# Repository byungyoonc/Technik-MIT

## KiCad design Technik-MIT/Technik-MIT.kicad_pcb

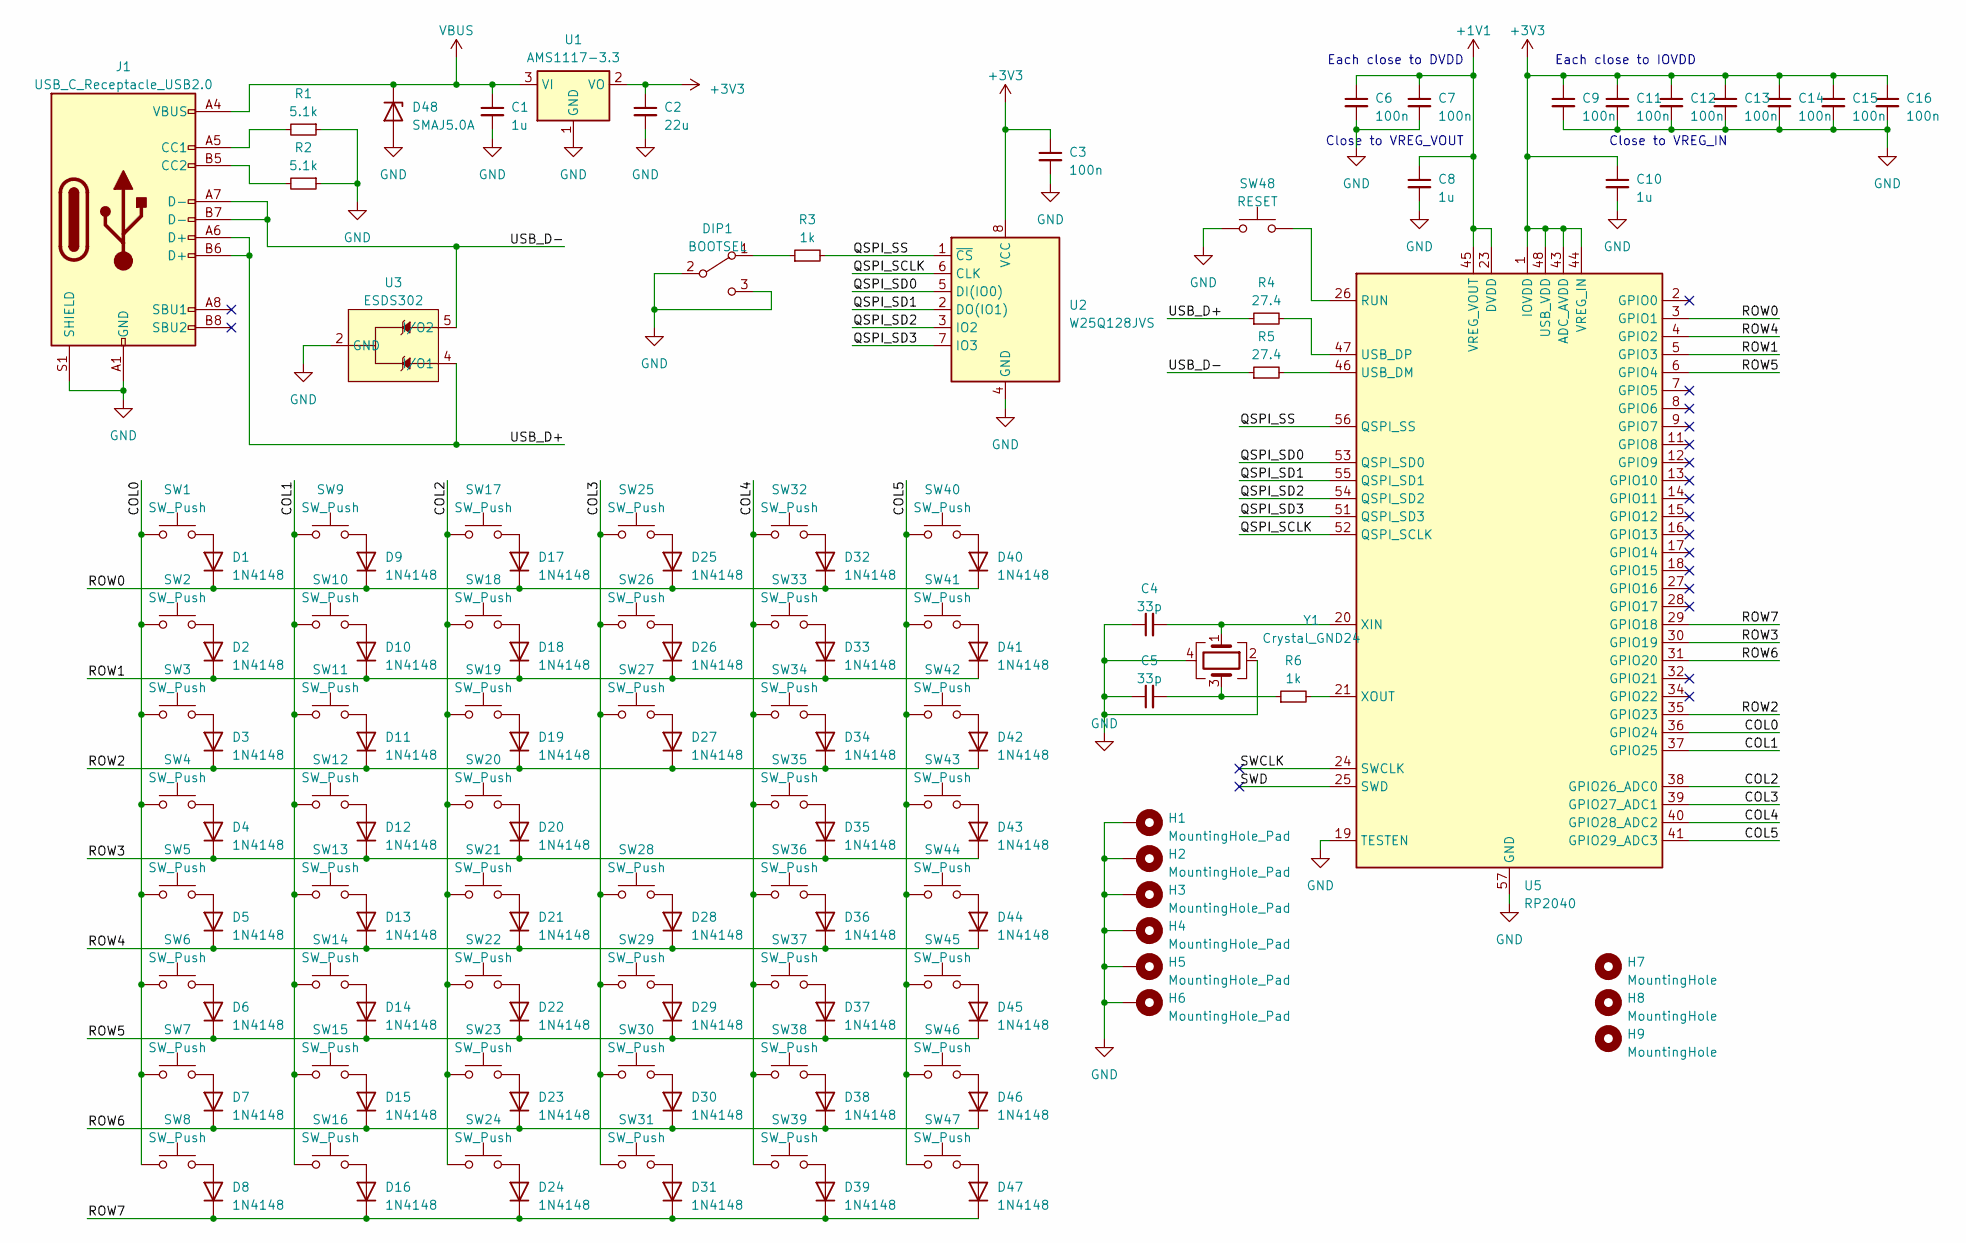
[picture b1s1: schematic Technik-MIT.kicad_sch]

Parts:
C1, C8, C10: 1u; C_0402_1005Metric
C2: 22u; C_0603_1608Metric
C3, C6, C7, C9, C11, C12, C13, C14, C15, C16: 100n; C_0402_1005Metric
C4, C5: 33p; C_0402_1005Metric
D1, D2, D3, D4, D5, D6, D7, D8, D9, D10, D11, D12, D13, D14, D15, D16, D17, D18, D19, D20, D21, D22, D23, D24, D25, D26, D27, D28, D29, D30, D31, D32, D33, D34, D35, D36, D37, D38, D39, D40, D41, D42, D43, D44, D45, D46, D47: 1N4148; D_SOD-123
D48: SMAJ5.0A; D_SMA; LCSC C2925443
DIP1: BOOTSEL; SW_SPDT_PCM12; LCSC C431541
H1, H2, H3, H4, H5, H6: MountingHole_Pad; Standoff_Hole
H7, H8, H9: MountingHole; Tooling Hole
J1: USB_C_Receptacle_USB2.0; Molex-216990_GCT-USB45xx_HRO-TYPE-C-31-M-13x; LCSC C3019717
R1, R2: 5.1k; R_0402_1005Metric
R3, R6: 1k; R_0402_1005Metric
R4, R5: 27.4; R_0603_1608Metric
SW1, SW2, SW3, SW4, SW5, SW6, SW7, SW8, SW9, SW10, SW11, SW12, SW13, SW14, SW15, SW16, SW17, SW18, SW19, SW20, SW21, SW22, SW23, SW24, SW25, SW26, SW27, SW28, SW29, SW30, SW31, SW32, SW33, SW34, SW35, SW36, SW37, SW38, SW39, SW41, SW42, SW43, SW45, SW46, SW47: SW_Push; ChocV1_Hotswap
SW40: SW_Push; ChocV1_Hotswap_WO_UpperRight
SW44: SW_Push; ChocV1_Hotswap_WO_UpperLeft
SW48: RESET; SW_SPST_TL3342; LCSC C318884
U1: AMS1117-3.3; SOT-223-3_TabPin2
U2: W25Q128JVS; SOIC-8_5.23x5.23mm_P1.27mm; LCSC C97521
U3: ESDS302; SOT-23-5
U5: RP2040; QFN-56-1EP_7x7mm_P0.4mm_EP3.2x3.2mm
Y1: Crystal_GND24; Crystal_SMD_3225-4Pin_3.2x2.5mm; LCSC C9002

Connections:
+1V1: C6.1, C7.1, C8.1, U5.23 (DVDD), U5.45 (VREG_VOUT), U5.50 (DVDD)
+3V3: C2.1, C3.1, C9.1, C10.1, C11.1, C12.1, C13.1, C14.1, C15.1, C16.1, U1.2 (VO), U2.8 (VCC), U5.1 (IOVDD), U5.10 (IOVDD), U5.22 (IOVDD), U5.33 (IOVDD), U5.42 (IOVDD), U5.43 (ADC_AVDD), U5.44 (VREG_IN), U5.48 (USB_VDD), U5.49 (IOVDD)
/COL0: SW1.1, SW2.1, SW3.1, SW4.1, SW5.1, SW6.1, SW7.1, SW8.1, U5.36 (GPIO24)
/COL1: SW9.1, SW10.1, SW11.1, SW12.1, SW13.1, SW14.1, SW15.1, SW16.1, U5.37 (GPIO25)
/COL2: SW17.1, SW18.1, SW19.1, SW20.1, SW21.1, SW22.1, SW23.1, SW24.1, U5.38 (GPIO26_ADC0)
/COL3: SW25.1, SW26.1, SW27.1, SW28.1, SW29.1, SW30.1, SW31.1, U5.39 (GPIO27_ADC1)
/COL4: SW32.1, SW33.1, SW34.1, SW35.1, SW36.1, SW37.1, SW38.1, SW39.1, U5.40 (GPIO28_ADC2)
/COL5: SW40.1, SW41.1, SW42.1, SW43.1, SW44.1, SW45.1, SW46.1, SW47.1, U5.41 (GPIO29_ADC3)
/QSPI_SCLK: U2.6 (CLK), U5.52 (QSPI_SCLK)
/QSPI_SD0: U2.5 (DI(IO0)), U5.53 (QSPI_SD0)
/QSPI_SD1: U2.2 (DO(IO1)), U5.55 (QSPI_SD1)
/QSPI_SD2: U2.3 (IO2), U5.54 (QSPI_SD2)
/QSPI_SD3: U2.7 (IO3), U5.51 (QSPI_SD3)
/QSPI_SS: R3.2, U2.1 (~CS), U5.56 (QSPI_SS)
/ROW0: D1.1 (K), D9.1 (K), D17.1 (K), D25.1 (K), D32.1 (K), D40.1 (K), U5.3 (GPIO1)
/ROW1: D2.1 (K), D10.1 (K), D18.1 (K), D26.1 (K), D33.1 (K), D41.1 (K), U5.5 (GPIO3)
/ROW2: D3.1 (K), D11.1 (K), D19.1 (K), D27.1 (K), D34.1 (K), D42.1 (K), U5.35 (GPIO23)
/ROW3: D4.1 (K), D12.1 (K), D20.1 (K), D35.1 (K), D43.1 (K), U5.30 (GPIO19)
/ROW4: D5.1 (K), D13.1 (K), D21.1 (K), D28.1 (K), D36.1 (K), D44.1 (K), U5.4 (GPIO2)
/ROW5: D6.1 (K), D14.1 (K), D22.1 (K), D29.1 (K), D37.1 (K), D45.1 (K), U5.6 (GPIO4)
/ROW6: D7.1 (K), D15.1 (K), D23.1 (K), D30.1 (K), D38.1 (K), D46.1 (K), U5.31 (GPIO20)
/ROW7: D8.1 (K), D16.1 (K), D24.1 (K), D31.1 (K), D39.1 (K), D47.1 (K), U5.29 (GPIO18)
/SWCLK: U5.24 (SWCLK)
/SWD: U5.25 (SWD)
/USB_D+: J1.A6 (D+), J1.B6 (D+), R4.1, U3.3 (NC), U3.4 (I/O1)
/USB_D-: J1.A7 (D-), J1.B7 (D-), R5.1, U3.1 (NC), U3.5 (I/O2)
GND: C1.2, C2.2, C3.2, C4.1, C5.1, C6.2, C7.2, C8.2, C9.2, C10.2, C11.2, C12.2, C13.2, C14.2, C15.2, C16.2, D48.2 (A), DIP1.2 (B), DIP1.3 (C), H1.1, H2.1, H3.1, H4.1, H5.1, H6.1, J1.A1 (GND), J1.A12 (GND), J1.B1 (GND), J1.B12 (GND), J1.S1 (SHIELD), R1.1, R2.1, SW48.1, U1.1 (GND), U2.4 (GND), U3.2 (GND), U5.19 (TESTEN), U5.57 (GND), Y1.2, Y1.4; also elsewhere on the board
unnamed: C5.2, R6.1, Y1.3
unnamed: D1.2 (A), SW1.2
unnamed: D2.2 (A), SW2.2
unnamed: D3.2 (A), SW3.2
unnamed: D4.2 (A), SW4.2
unnamed: D5.2 (A), SW5.2
unnamed: D6.2 (A), SW6.2
unnamed: D7.2 (A), SW7.2
unnamed: D8.2 (A), SW8.2
unnamed: D9.2 (A), SW9.2
unnamed: D10.2 (A), SW10.2
unnamed: D11.2 (A), SW11.2
unnamed: D12.2 (A), SW12.2
unnamed: D13.2 (A), SW13.2
unnamed: D14.2 (A), SW14.2
unnamed: D15.2 (A), SW15.2
unnamed: D16.2 (A), SW16.2
unnamed: D17.2 (A), SW17.2
unnamed: D18.2 (A), SW18.2
unnamed: D19.2 (A), SW19.2
unnamed: D20.2 (A), SW20.2
unnamed: D21.2 (A), SW21.2
unnamed: D22.2 (A), SW22.2
unnamed: D23.2 (A), SW23.2
unnamed: D24.2 (A), SW24.2
unnamed: D25.2 (A), SW25.2
unnamed: D26.2 (A), SW26.2
unnamed: D27.2 (A), SW27.2
unnamed: D28.2 (A), SW28.2
unnamed: D29.2 (A), SW29.2
unnamed: D30.2 (A), SW30.2
unnamed: D31.2 (A), SW31.2
unnamed: D32.2 (A), SW32.2
unnamed: D33.2 (A), SW33.2
unnamed: D34.2 (A), SW34.2
unnamed: D35.2 (A), SW35.2
unnamed: D36.2 (A), SW36.2
unnamed: D37.2 (A), SW37.2
unnamed: D38.2 (A), SW38.2
unnamed: D39.2 (A), SW39.2
unnamed: D40.2 (A), SW40.2
unnamed: D41.2 (A), SW41.2
unnamed: D42.2 (A), SW42.2
unnamed: D43.2 (A), SW43.2
unnamed: D44.2 (A), SW44.2
unnamed: D45.2 (A), SW45.2
unnamed: D46.2 (A), SW46.2
unnamed: D47.2 (A), SW47.2
unnamed 75: DIP1.1 (A), R3.1; also elsewhere on the board
unnamed: J1.A5 (CC1), R1.2
unnamed: J1.B5 (CC2), R2.2
unnamed 78: SW48.2, U5.26 (RUN); also elsewhere on the board
unnamed: R5.2, U5.46 (USB_DM)
unnamed: R4.2, U5.47 (USB_DP)
unnamed: C4.2, U5.20 (XIN), Y1.1
unnamed: R6.2, U5.21 (XOUT)
VBUS: C1.1, D48.1 (K), J1.A4 (VBUS), J1.A9 (VBUS), J1.B4 (VBUS), J1.B9 (VBUS), U1.3 (VI)

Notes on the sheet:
Close to VREG_VOUT
Close to VREG_IN
Each close to DVDD
Each close to IOVDD

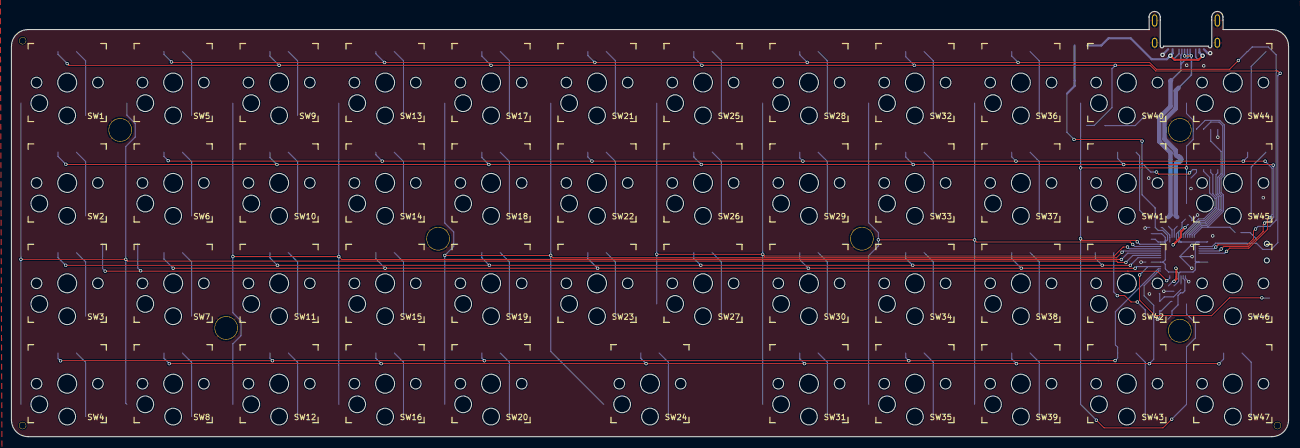
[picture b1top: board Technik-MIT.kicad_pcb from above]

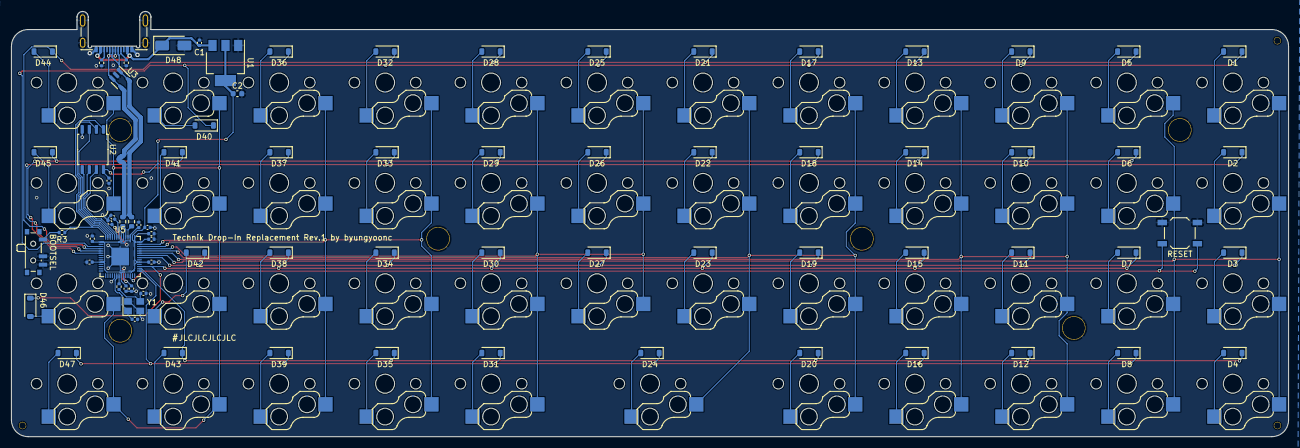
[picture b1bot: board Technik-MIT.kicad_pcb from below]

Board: 2 copper layers, 229.0 x 76.2 mm, 134 parts (78 on the bottom side), 82 nets.

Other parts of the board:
BOOTSEL: BOOTSEL; SW_SPDT_PCM12
RESET: RESET; SW_SPST_TL3342

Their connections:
GND: BOOTSEL.2 (B), BOOTSEL.3 (C), RESET.1; also elsewhere on the board
unnamed 75: BOOTSEL.1 (A); also elsewhere on the board
unnamed 78: RESET.2; also elsewhere on the board

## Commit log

2023-03-19 Initialize KiCad project
2023-03-19 Add submodules
2023-03-19 Add submodule
2023-03-19 Update library
2023-03-22 Update PCB schematics
2023-03-23 Update PCB schematics (again)
2023-03-24 Update PCB schematic
2023-03-24 Update PCB
2023-03-27 Working on PCB
2023-04-09 Update PCB
    Change spacing from MX to Choc
2023-04-10 Update ChocV1_Hotswap footprint
2023-04-13 Update PCB to match preexisting mounting holes
2023-04-13 Update some of the silkscreen
2023-04-16 Update fabrication export settings
    Alongside with some minor trace update
2023-04-17 Add tooling holes, JLC order number silkscreen.
2023-04-30 Finalizing PCB layout for print
2023-05-10 Added symbol for ESDS302
2023-05-10 Changed PCB layout & schematics for cheaper production at JLCPCB
    Used available basic parts alternatives
2023-05-10 Adjusted silkscreen position
2023-05-11 Updated PCB layout to avoid interferences
2023-05-11 Added top plate project files
